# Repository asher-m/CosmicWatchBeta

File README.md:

# CosmicWatchBeta
An iteration on the Cosmic Watch by MIT, or at least some of it.  See http://cosmicwatch.lns.mit.edu/ for more details.

The design iterations made in this project are from or for University of New Hampshire's Physics 605: Experimental Physics class, for Asher Merrill's final project.

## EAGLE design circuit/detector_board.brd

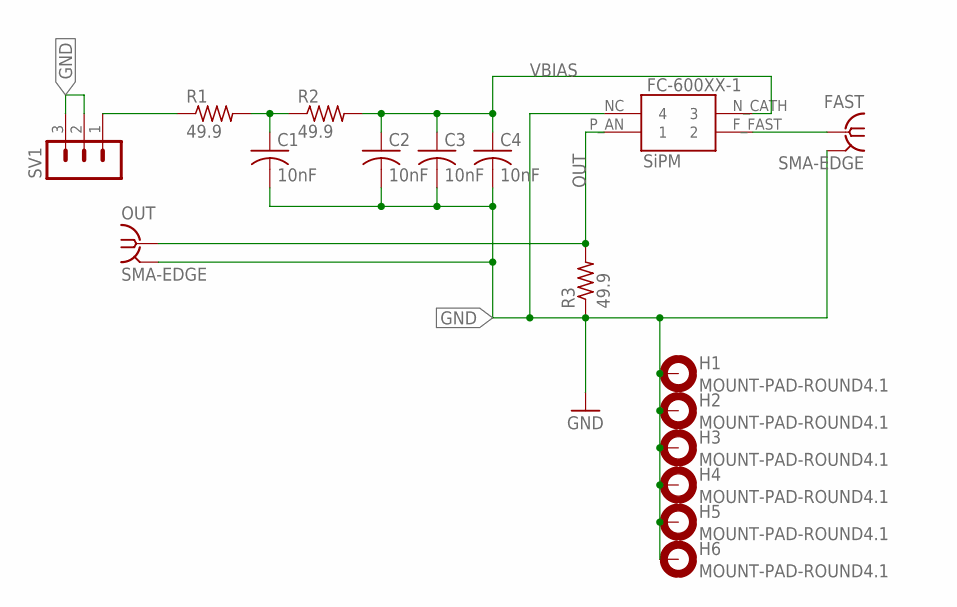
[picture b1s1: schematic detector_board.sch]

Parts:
C1, C2, C3, C4: 10nF; C0603
FAST: SMA-EDGE
FC-600XX-1: SiPM; FC-600XX-SMT_FULL
H1, H2, H3, H4, H5, H6: MOUNT-PAD-ROUND4.1; 4,1-PAD
OUT: SMA-EDGE
R1, R2, R3: 49.9; R0603
SV1: MA03-1

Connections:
FAST: FAST.G@0 (1), FC-600XX-1.F_FAST (2)
GND: C1.2, C2.2, C3.2, C4.2, FAST.G@1 (2), FAST.G@2 (2), FAST.G@3 (2), FAST.G@4 (2), FC-600XX-1.NC (4), H1.B4,1, H2.B4,1, H3.B4,1, H4.B4,1, H5.B4,1, H6.B4,1, OUT.G@1 (2), OUT.G@2 (2), OUT.G@3 (2), OUT.G@4 (2), R3.1, SV1.2, SV1.3
IN: R1.1, SV1.1
OUT: FC-600XX-1.P_AN (1), OUT.G@0 (1), R3.2
P1: C1.1, R1.2, R2.1
VBIAS: C2.1, C3.1, C4.1, FC-600XX-1.N_CATH (3), R2.2

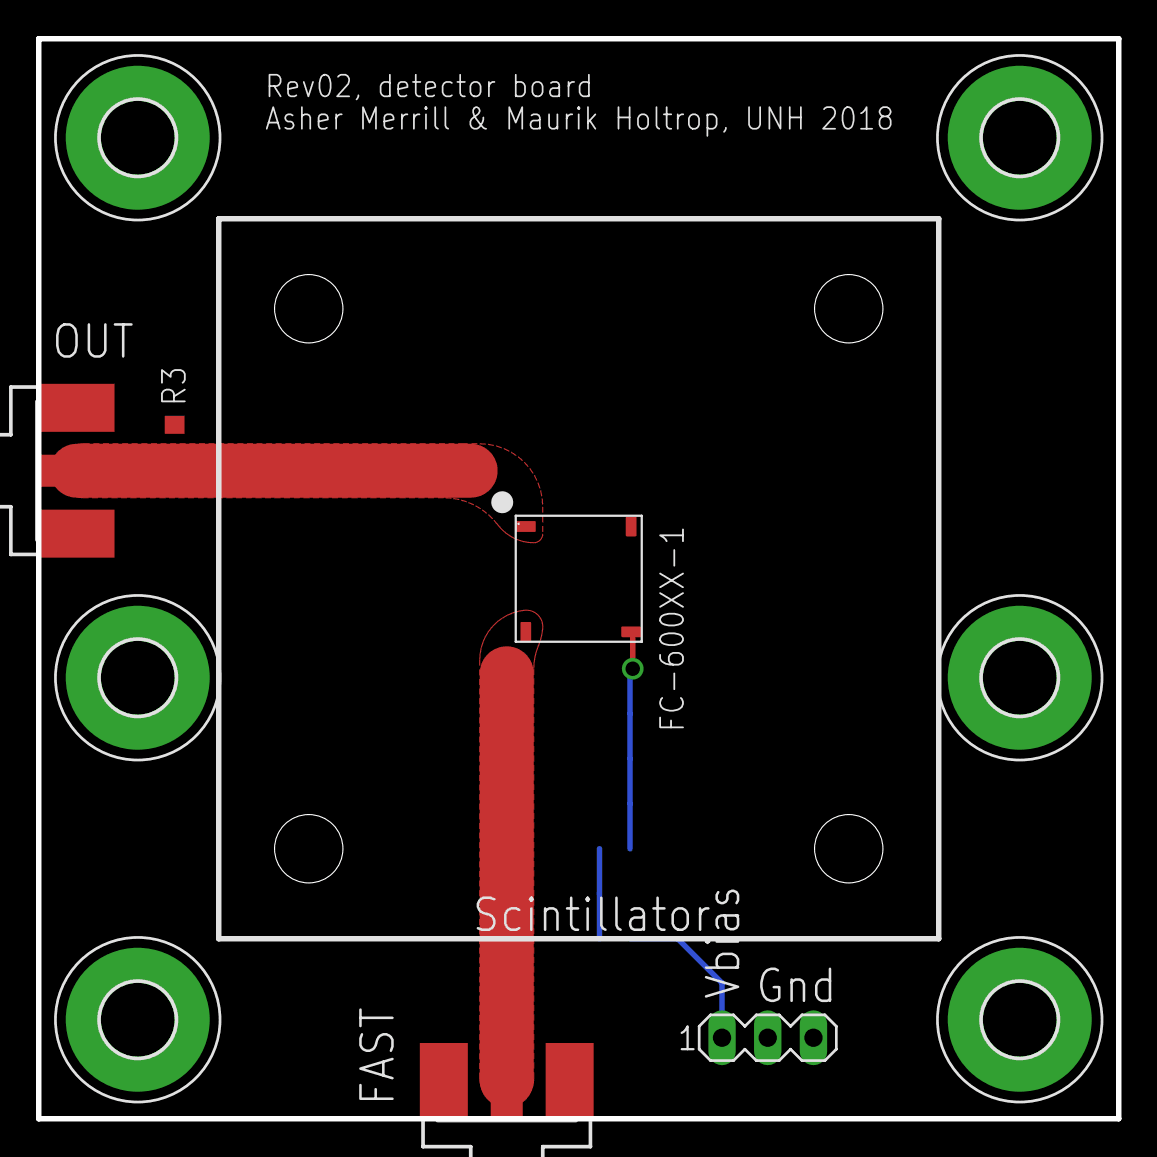
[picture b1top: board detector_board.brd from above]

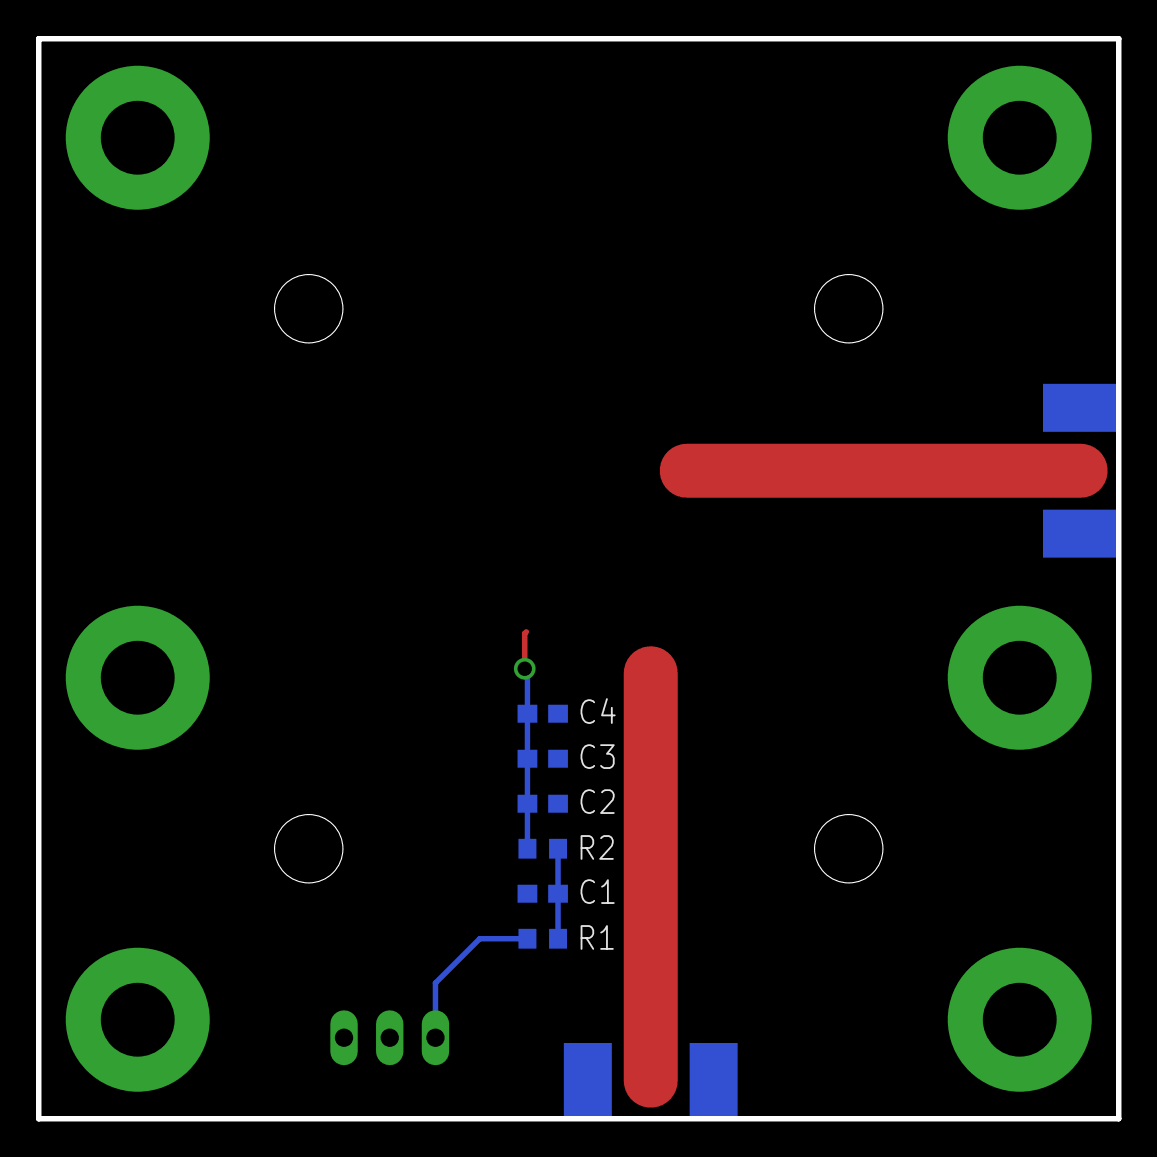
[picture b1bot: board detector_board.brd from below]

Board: 2 copper layers, 60.0 x 60.0 mm, 17 parts (6 on the bottom side), 6 nets.

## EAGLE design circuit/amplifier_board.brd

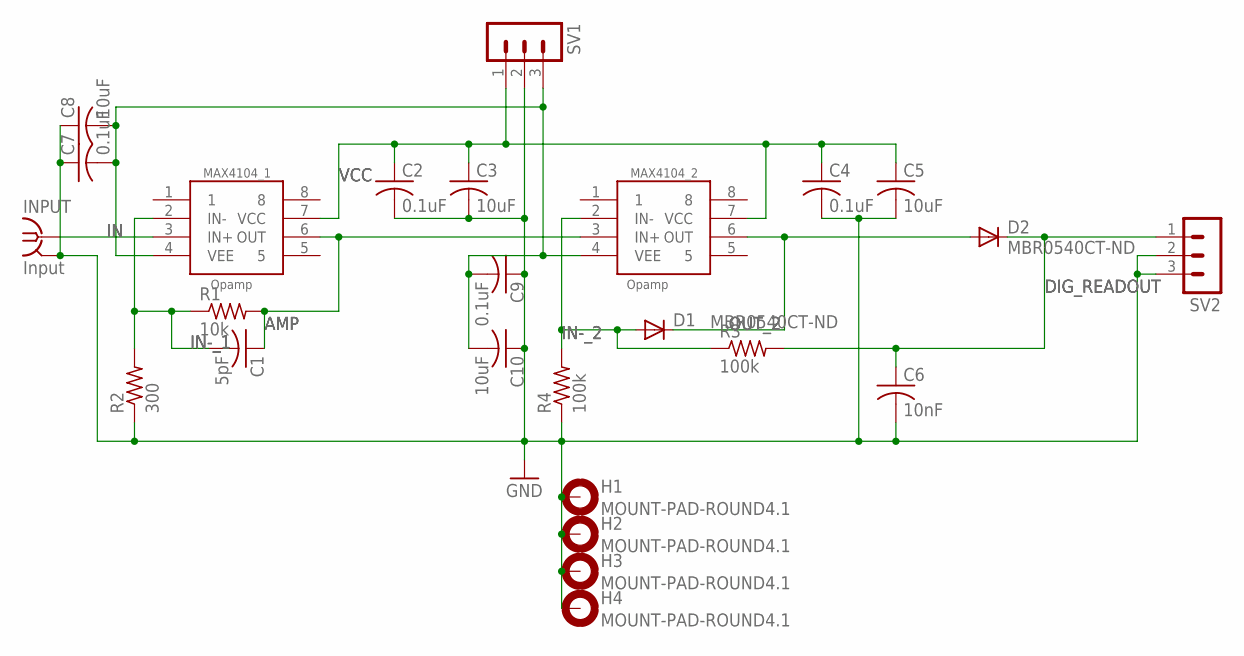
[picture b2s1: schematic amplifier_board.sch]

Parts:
C1: 5pF; C0603
C2, C4, C7, C9: 0.1uF; C0603
C3, C5, C8, C10: 10uF; C0603
C6: 10nF; C0603
D1, D2: MBR0540CT-ND; SOD-123_MINI-SMA
H1, H2, H3, H4: MOUNT-PAD-ROUND4.1; 4,1-PAD
INPUT: Input; SMA-EDGE
MAX4104_1, MAX4104_2: Opamp; SO8
R1: 10k; R0603
R2: 300; R0603
R3, R4: 100k; R0603
SV1, SV2: MA03-1

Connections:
AMP: C1.1, MAX4104_1.6 (OUT), MAX4104_2.3 (IN+), R1.2
DIG_READOUT: C6.1, D2.C, R3.2, SV2.1
GND: C2.2, C3.2, C4.2, C5.2, C6.2, C7.1, C8.1, C9.1, C10.1, H1.B4,1, H2.B4,1, H3.B4,1, H4.B4,1, INPUT.G@1 (2), INPUT.G@2 (2), INPUT.G@3 (2), INPUT.G@4 (2), R2.1, R4.1, SV1.2, SV2.2, SV2.3
IN: INPUT.G@0 (1), MAX4104_1.3 (IN+)
IN-_1: C1.2, MAX4104_1.2 (IN-), R1.1, R2.2
IN-_2: D1.A, MAX4104_2.2 (IN-), R3.1, R4.2
OUT_2: D1.C, D2.A, MAX4104_2.6 (OUT)
VCC: C2.1, C3.1, C4.1, C5.1, MAX4104_1.7 (VCC), MAX4104_2.7 (VCC), SV1.1
VEE: C7.2, C8.2, C9.2, C10.2, MAX4104_1.4 (VEE), MAX4104_2.4 (VEE), SV1.3

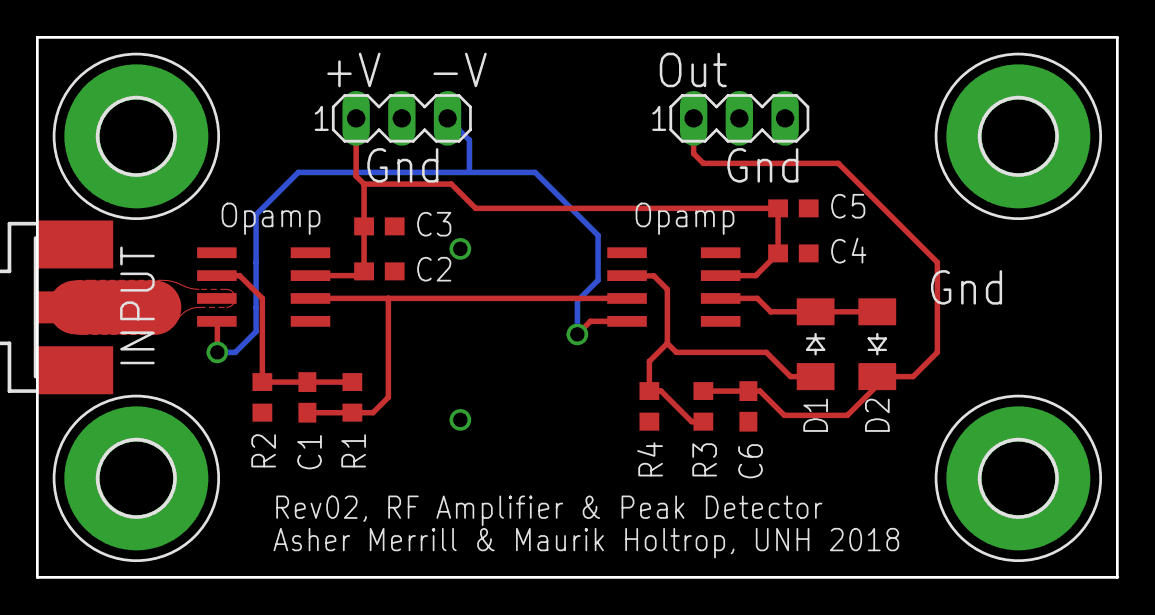
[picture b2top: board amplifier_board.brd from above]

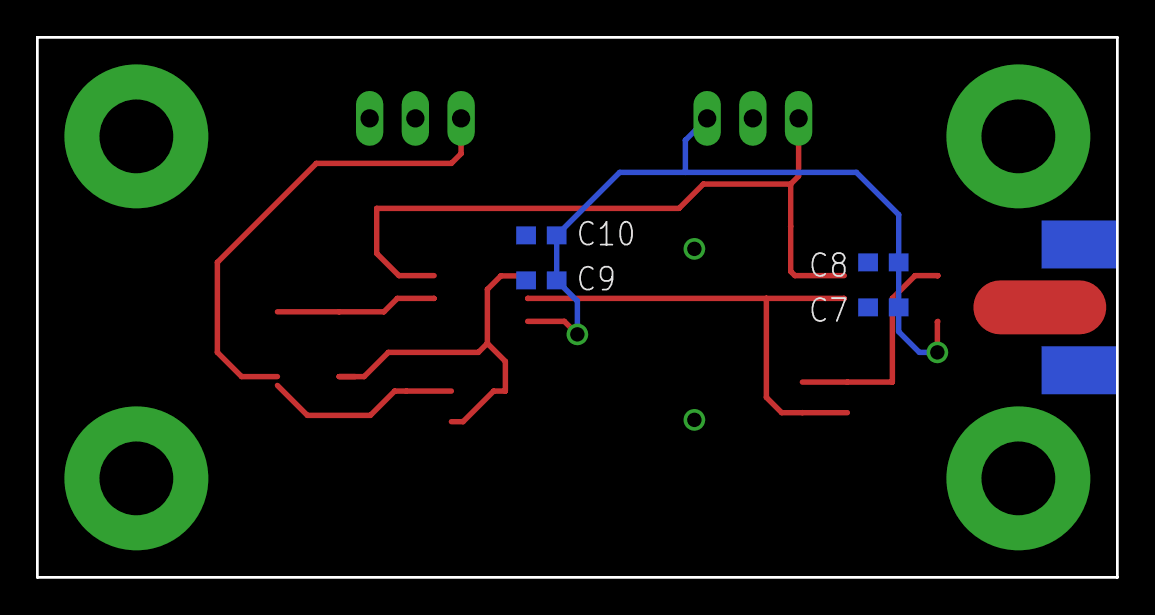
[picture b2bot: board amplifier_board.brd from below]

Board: 2 copper layers, 60.0 x 30.0 mm, 25 parts (4 on the bottom side), 9 nets.

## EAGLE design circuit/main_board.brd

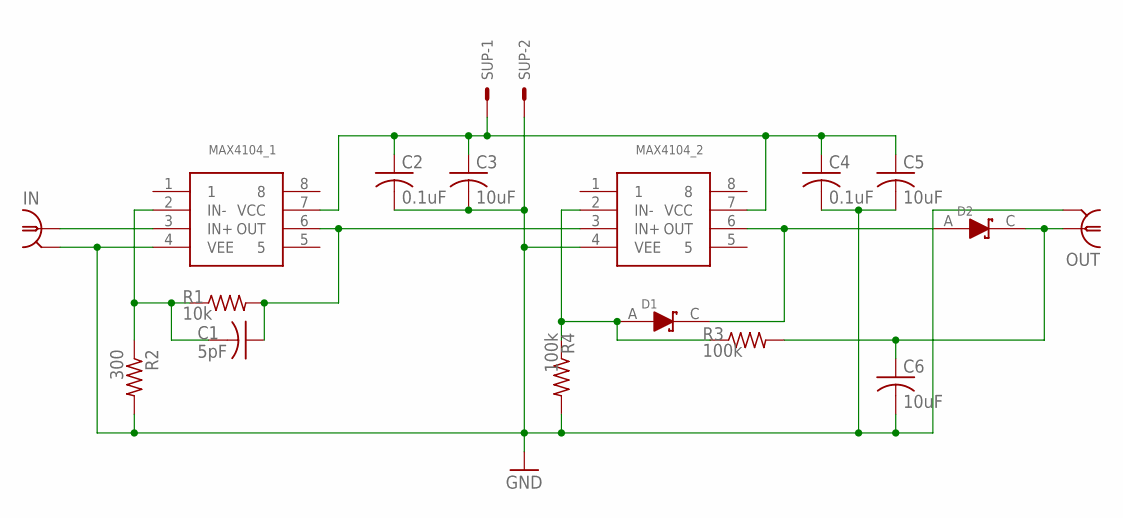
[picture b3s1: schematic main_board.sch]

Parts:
C1: 5pF; C0805
C2, C4: 0.1uF; C0805
C3, C5, C6: 10uF; C0805
D1, D2: SCH_D1; SML0805
IN: LTI-SASF54GT
MAX4104_1, MAX4104_2: MAX4104; SO8
OUT: LTI-SASF54GT
R1: 10k; M0805
R2: 300; M0805
R3, R4: 100k; M0805
SUP: 332-02

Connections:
AMP: C1.1, MAX4104_1.6 (OUT), MAX4104_2.3 (IN+), R1.2
DIG_READOUT: C6.1, D2.C (OUT), OUT.1, R3.2
GND: C2.2, C3.2, C4.2, C5.2, C6.2, IN.2, IN.3 (2), IN.4 (2), IN.5 (2), MAX4104_1.4 (VEE), MAX4104_2.4 (VEE), OUT.2, OUT.3 (2), OUT.4 (2), OUT.5 (2), R2.2, R4.2, SUP.2
IN: IN.1, MAX4104_1.3 (IN+)
IN-_1: C1.2, MAX4104_1.2 (IN-), R1.1, R2.1
IN-_2: D1.A (IN), MAX4104_2.2 (IN-), R3.1, R4.1
OUT_2: D1.C (OUT), D2.A (IN), MAX4104_2.6 (OUT)
VCC: C2.1, C3.1, C4.1, C5.1, MAX4104_1.7 (VCC), MAX4104_2.7 (VCC), SUP.1

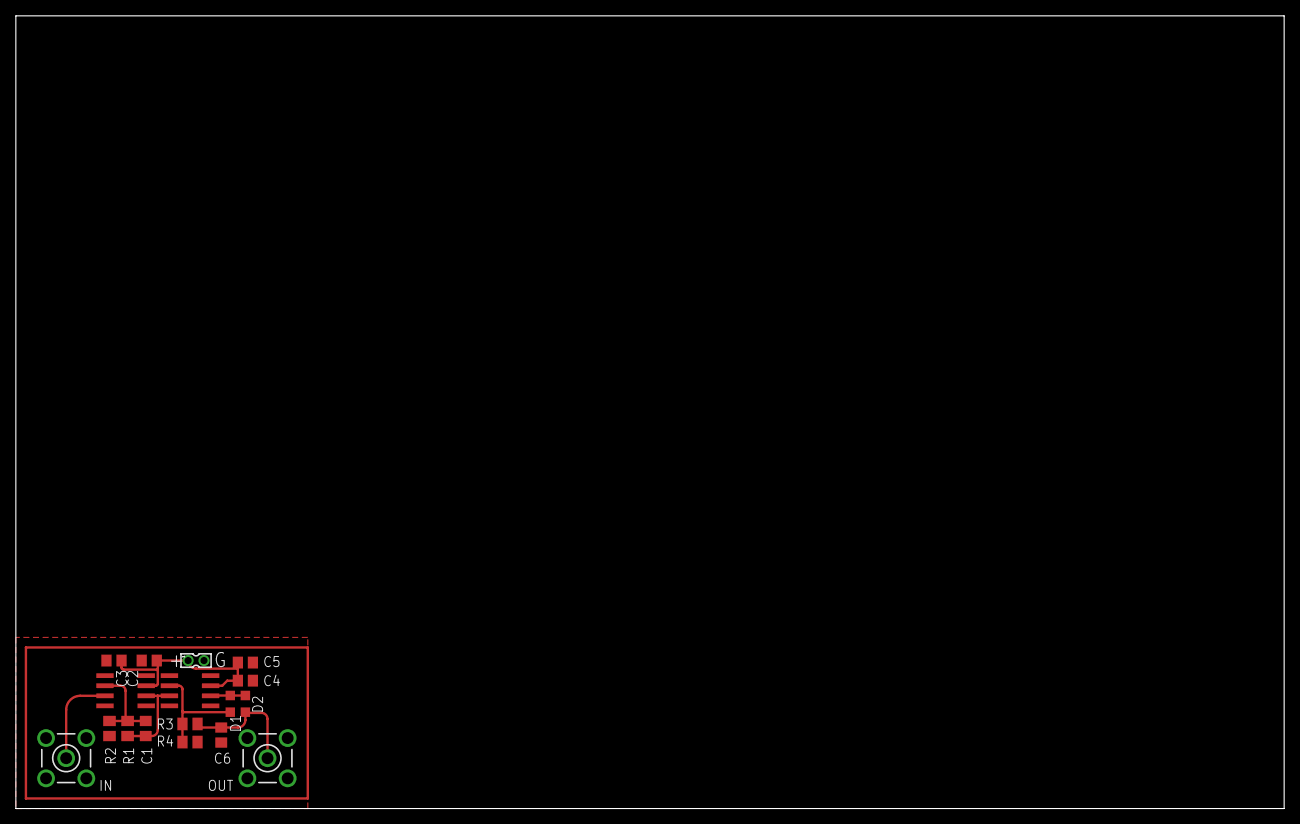
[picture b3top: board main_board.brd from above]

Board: 2 copper layers, 160.0 x 100.0 mm, 17 parts (0 on the bottom side), 8 nets.

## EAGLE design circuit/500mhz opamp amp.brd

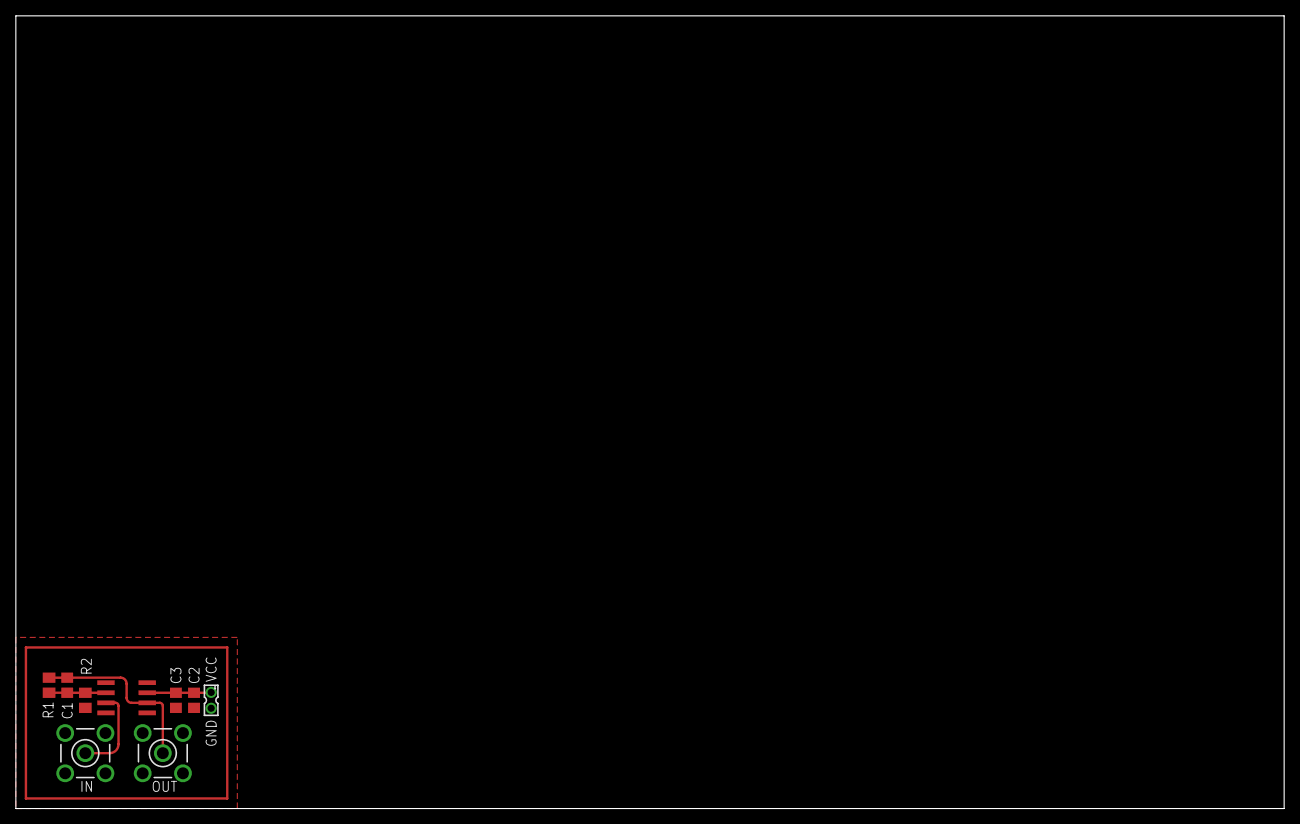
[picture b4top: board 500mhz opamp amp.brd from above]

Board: 2 copper layers, 160.0 x 100.0 mm, 9 parts (0 on the bottom side), 5 nets.

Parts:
C1: C0805
C2: 10uF; C0805
C3: 0.1uF; C0805
IN: LTI-SASF54GT
MAX4104_1: SO8
OUT: LTI-SASF54GT
R1, R2: M0805
SUP: 332-02

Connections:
GND: C2.2, C3.2, IN.2, IN.3, IN.4, IN.5, MAX4104_1.4, OUT.2, OUT.3, OUT.4, OUT.5, R2.2, SUP.2
IN-: C1.2, MAX4104_1.2, R1.1, R2.1
unnamed: C2.1, C3.1, MAX4104_1.7, SUP.1
VIN: IN.1, MAX4104_1.3
VOUT: C1.1, MAX4104_1.6, OUT.1, R1.2

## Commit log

2018-04-14 Added .gitignore
    Added .gitignore so we don't commit anything we don't want. Generated online for C, Python and Eagle.
2018-04-14 Added amplifier schematic and board
    Added amplfiier schematic and board so we can sensibly start collaboration.
2018-04-14 Renamed files
2018-04-14 Added parts library for Phys 605
    You will need to add the library to Eagle in order to be able to open the schematic.
2018-04-14 Added Schottky diode to Library; added Peak Detector to Schematic and Board
2018-04-17 Uploaded documentation of SensL MicroFC-60035-SMT and created Docs dir.
2018-04-17 Updated README.md for docs
2018-04-17 Removed Schottky diode; found correct package/device inside default libraries.
2018-04-17 boards: Changed components to be correct; increased board size to be solderable.
2018-04-17 boards: Increased trace clearance for easier hand soldering; reworked some traces so ground path isn't as long
2018-04-18 Updated/corrected docs for the correct part.
2018-04-18 Created detector board and device in Eagle library.
2018-04-18 docs: Updated readme; added manual for SensL Micro_C products
2018-04-18 boards: Added script to copy updated library to lbr directory for Eagle
    Note that, of course, this script only works on my local machine(s, incidentally I have Eagle in the same place(s) on both.) You'll have to change this or make it work differently if using UNIX.
2018-04-18 boards: Added script to copy back library after updating and moved other script.
2018-04-18 boards: Updated library for a bit easier use with the detector.
2018-04-19 Fixed/perfected FC-600XX package, keepout zones. Removed hand-solder package while deprecated.
2018-04-19 Fixed inconsistent keepout spacing around 600XX package.
2018-04-19 boards; docs: Updated docs with impedance calculator; updated board design to stack, be solderable, and use new package design for FC-600XX.
2018-04-19 boards: Committed overall prototype design as well as CosmicWatch normal design.
2018-04-19 boards: Changes to library and board designs.
    Will I need to remove the vias and replace them with holes in order to be able to ground both sides?
2018-04-19 boards: Changes to amplifier board board.
2018-04-20 boards: Simplified both boards
2018-04-20 boards: Rev00_ss ready
2018-04-20 boards: Rev00_ds ready
2018-04-20 boards: Changed packages of cap and resistors to be 0603, as we will have available. Also changed mount points to be grounded, and made vias solderable.
2018-04-20 boards: Added text.
2018-04-20 Modified board. Tried to add Spice model.
2018-04-23 boards: Added VEE line to header. Corrected header to be 0.100", (what we have in stock,) not 2mm header.
    Also added filtering caps (backwards, sort of,) to stabilize the VEE line.
2018-04-24 cam: Created CAM directory with most recent files.
    These will most likely only be updated on production, but it's nice to have the files somewhere.
2018-04-27 boards: Needed more clearance on pads under sensor, so removed ground plane under detector.
2018-04-27 Post processor: Added CAM file for Eagle to get to LPKF mill.
2018-04-27 cam: Moved LPKF CAM processor.
2018-04-27 CAM: Changed CAM to new boards, sent to Jim.
2018-04-27 CAM: 274X option apparently does nothing in the CAM processor.
2018-04-29 boards: Increased trace width so Jim can actually mill the boards.
2018-04-29 cam: Updated CAM to give to Jim.
2018-10-06 final report: Added final report for reference purposes for future research.
